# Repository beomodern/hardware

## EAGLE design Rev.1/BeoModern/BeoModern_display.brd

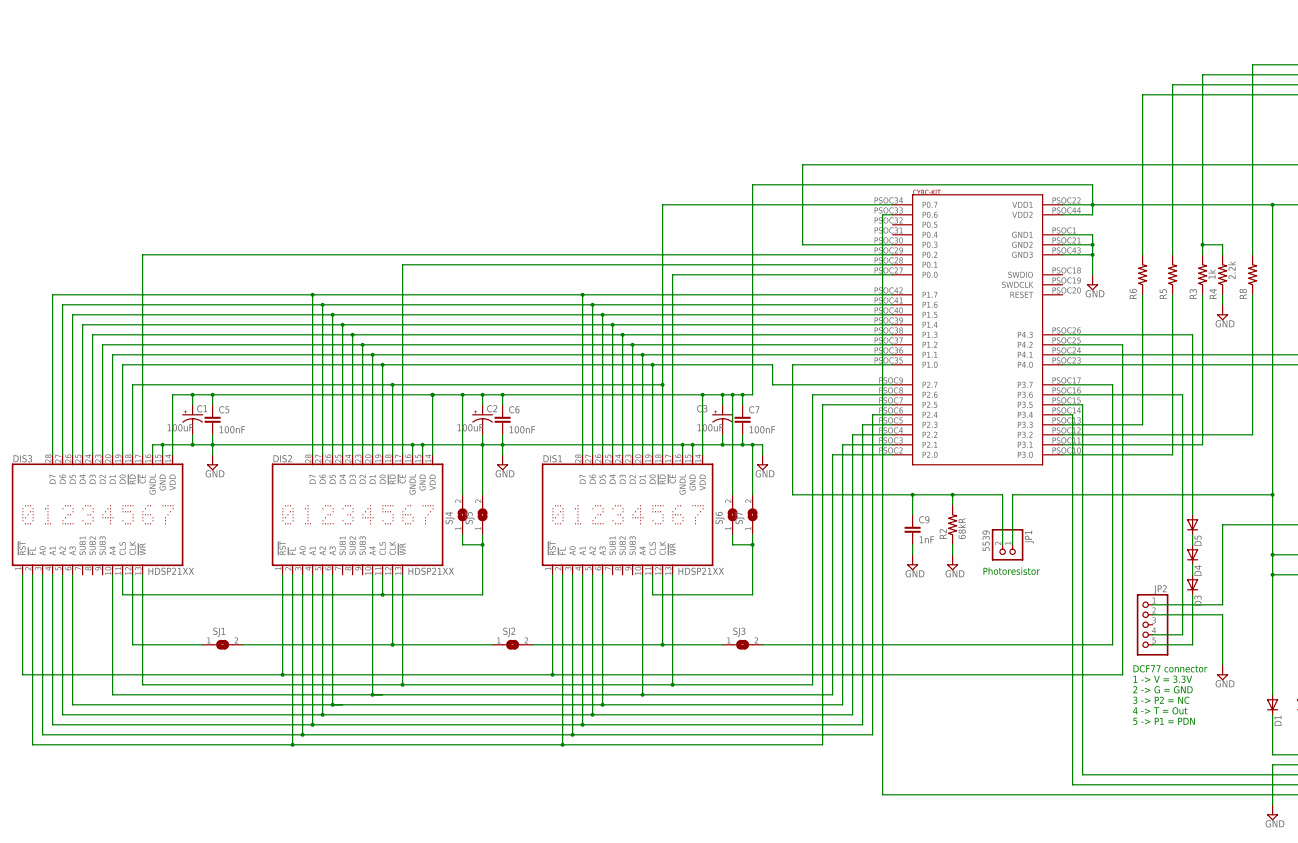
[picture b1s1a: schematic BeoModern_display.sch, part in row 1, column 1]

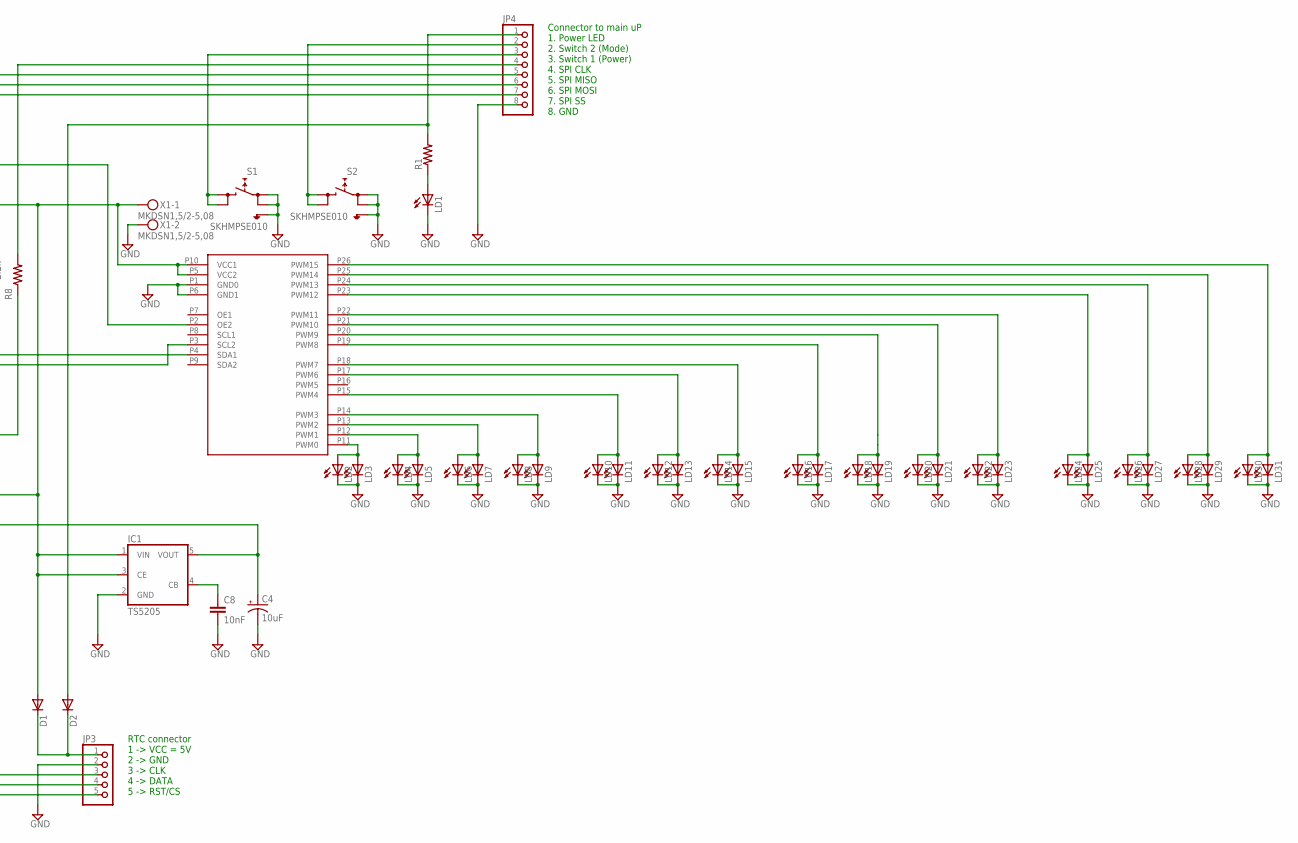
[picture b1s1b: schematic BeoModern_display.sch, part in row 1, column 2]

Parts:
C1, C2, C3: 100uF; E15-5
C4: 10uF; E2,5-5
C5, C6, C7: 100nF; C15B5
C8: 10nF; C2.5-2
C9: 1nF; C2.5-2
D1, D2, D3, D4, D5: DIODE-SOD80C; SOD80C
DIS1, DIS2, DIS3: HDSP21XX
IC1: TS5205; SOT25
JP1: 5539; 1X02
JP2, JP3: PINHD-1X5; 1X05
JP4: PINHD-1X8; 1X08
LD1, LD2, LD3, LD4, LD5, LD6, LD7, LD8, LD9, LD10, LD11, LD12, LD13, LD14, LD15, LD16, LD17, LD18, LD19, LD20, LD21, LD22, LD23, LD24, LD25, LD26, LD27, LD28, LD29, LD30, LD31: TLLR4400; LED3MM
R1, R5, R6, R8: R-US_0207/10; 0207/10
R2: 68kR; 0207/10
R3: 1k; 0207/10
R4: 2.2k; 0207/10
S1, S2: SKHMPSE010; SKHMPXE010
SJ1, SJ2, SJ3, SJ4, SJ5, SJ6, SJ7: SJ
U$9: CY8C-KIT; CY8C-KIT-FOOTPRINT
U$10: PCA9685; PCA9685_FOOTPRINT
X1: MKDSN1,5/2-5,08

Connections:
GND: C1.-, C2.-, C3.-, C4.-, C5.2, C6.2, C7.2, C8.2, C9.2, DIS1.15 (GND), DIS1.16 (GNDL), DIS2.15 (GND), DIS2.16 (GNDL), DIS3.15 (GND), DIS3.16 (GNDL), IC1.2 (GND), JP2.2, JP3.2, JP4.8, LD1.K (C), LD2.K (C), LD3.K (C), LD4.K (C), LD5.K (C), LD6.K (C), LD7.K (C), LD8.K (C), LD9.K (C), LD10.K (C), LD11.K (C), LD12.K (C), LD13.K (C), LD14.K (C), LD15.K (C), LD16.K (C), LD17.K (C), LD18.K (C), LD19.K (C), LD20.K (C), LD21.K (C), LD22.K (C), LD23.K (C), LD24.K (C), LD25.K (C), LD26.K (C), LD27.K (C), LD28.K (C), LD29.K (C), LD30.K (C), LD31.K (C), R2.1, R4.1, S1.1 (1.1), S1.2 (1.2), S1.5 (SH), S2.1 (1.1), S2.2 (1.2), S2.5 (SH), SJ5.2, SJ7.2, U$9.PSOC1 (GND1), U$9.PSOC21 (GND2), U$9.PSOC43 (GND3), U$10.P1 (GND0), U$10.P6 (GND1), X1.2
unnamed: LD14.A, LD15.A, U$10.P18 (PWM7)
unnamed: LD12.A, LD13.A, U$10.P17 (PWM6)
unnamed: U$9.PSOC24 (P4.1), U$10.P4 (SDA1)
unnamed: LD10.A, LD11.A, U$10.P15 (PWM4)
unnamed: LD1.A, R1.1
unnamed: JP2.4, U$9.PSOC16 (P3.6)
unnamed: U$9.PSOC23 (P4.0), U$10.P3 (SCL2)
unnamed: R5.1, U$9.PSOC10 (P3.0)
unnamed: LD30.A, LD31.A, U$10.P26 (PWM15)
unnamed: LD28.A, LD29.A, U$10.P25 (PWM14)
unnamed: LD26.A, LD27.A, U$10.P24 (PWM13)
unnamed: LD24.A, LD25.A, U$10.P23 (PWM12)
unnamed: R6.1, U$9.PSOC13 (P3.3)
unnamed: R8.1, U$9.PSOC12 (P3.2)
unnamed: JP4.6, R5.2
unnamed: JP4.4, R8.2
unnamed: JP4.7, R6.2
unnamed: DIS2.11 (CLS), DIS3.11 (CLS), SJ4.1, SJ5.1
unnamed: C8.1, IC1.4 (CB)
unnamed: JP4.2, S2.3 (2.1), S2.4 (2.2)
unnamed: D2.A, JP4.1, R1.2
unnamed: JP4.5, R3.2, R4.2
unnamed: DIS2.12 (CLK), SJ1.2, SJ2.1
unnamed: R3.1, U$9.PSOC11 (P3.1)
unnamed: SJ3.2, U$9.PSOC17 (P3.7)
unnamed: DIS1.12 (CLK), SJ2.2, SJ3.1
unnamed: DIS1.11 (CLS), SJ6.1, SJ7.1
unnamed: DIS3.12 (CLK), SJ1.1
unnamed: DIS1.19 (D0), DIS2.19 (D0), DIS3.19 (D0), U$9.PSOC9 (P2.7)
unnamed: DIS1.13 (!WR), DIS2.13 (!WR), DIS3.13 (!WR), U$9.PSOC8 (P2.6)
unnamed: DIS1.28 (D7), DIS2.28 (D7), DIS3.28 (D7), U$9.PSOC42 (P1.7)
unnamed: DIS1.27 (D6), DIS2.27 (D6), DIS3.27 (D6), U$9.PSOC41 (P1.6)
unnamed: DIS1.26 (D5), DIS2.26 (D5), DIS3.26 (D5), U$9.PSOC40 (P1.5)
unnamed: DIS1.25 (D4), DIS2.25 (D4), DIS3.25 (D4), U$9.PSOC39 (P1.4)
unnamed: DIS1.24 (D3), DIS2.24 (D3), DIS3.24 (D3), U$9.PSOC38 (P1.3)
unnamed: DIS1.23 (D2), DIS2.23 (D2), DIS3.23 (D2), U$9.PSOC37 (P1.2)
unnamed: DIS1.20 (D1), DIS2.20 (D1), DIS3.20 (D1), U$9.PSOC36 (P1.1)
unnamed: DIS1.18 (!RD), DIS2.18 (!RD), DIS3.18 (!RD), U$9.PSOC34 (P0.7)
unnamed: DIS3.17 (!CE), U$9.PSOC29 (P0.2)
unnamed: DIS2.17 (!CE), U$9.PSOC28 (P0.1)
unnamed: DIS1.17 (!CE), U$9.PSOC27 (P0.0)
unnamed: DIS1.10 (A4), DIS2.10 (A4), DIS3.10 (A4), U$9.PSOC2 (P2.0)
unnamed: DIS1.1 (!RST), DIS2.1 (!RST), DIS3.1 (!RST), U$9.PSOC25 (P4.2)
unnamed: DIS1.6 (A3), DIS2.6 (A3), DIS3.6 (A3), U$9.PSOC3 (P2.1)
unnamed: DIS1.5 (A2), DIS2.5 (A2), DIS3.5 (A2), U$9.PSOC4 (P2.2)
unnamed: DIS1.4 (A1), DIS2.4 (A1), DIS3.4 (A1), U$9.PSOC5 (P2.3)
unnamed: DIS1.3 (A0), DIS2.3 (A0), DIS3.3 (A0), U$9.PSOC6 (P2.4)
unnamed: DIS1.2 (!FL), DIS2.2 (!FL), DIS3.2 (!FL), U$9.PSOC7 (P2.5)
unnamed: U$9.PSOC30 (P0.3), U$10.P2 (OE2)
unnamed: D5.A, U$9.PSOC26 (P4.3)
unnamed: LD22.A, LD23.A, U$10.P22 (PWM11)
unnamed: LD20.A, LD21.A, U$10.P21 (PWM10)
unnamed: LD18.A, LD19.A, U$10.P20 (PWM9)
unnamed: LD16.A, LD17.A, U$10.P19 (PWM8)
unnamed: LD8.A, LD9.A, U$10.P14 (PWM3)
unnamed: LD6.A, LD7.A, U$10.P13 (PWM2)
unnamed: LD4.A, LD5.A, U$10.P12 (PWM1)
unnamed: LD2.A, LD3.A, U$10.P11 (PWM0)
unnamed: C4.+, IC1.5 (VOUT), JP2.1
unnamed: JP4.3, S1.3 (2.1), S1.4 (2.2)
unnamed: C9.1, JP1.2, R2.2, U$9.PSOC35 (P1.0)
unnamed: JP3.3, U$9.PSOC15 (P3.5)
unnamed: JP3.4, U$9.PSOC14 (P3.4)
unnamed: JP3.5, U$9.PSOC33 (P0.6)
unnamed: D3.C, JP2.5
unnamed: D4.A, D5.C
unnamed: D3.A, D4.C
unnamed: D1.C, D2.C, JP3.1
unnamed: C1.+, C2.+, C3.+, C5.1, C6.1, C7.1, D1.A, DIS1.14 (VDD), DIS2.14 (VDD), DIS3.14 (VDD), IC1.1 (VIN), IC1.3 (CE), JP1.1, SJ4.2, SJ6.2, U$9.PSOC22 (VDD1), U$9.PSOC44 (VDD2), U$10.P5 (VCC2), U$10.P10 (VCC1), X1.1

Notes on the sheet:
DCF77 connector 1 -> V = 3.3V 2 -> G = GND 3 -> P2 = NC 4 -> T = Out 5 -> P1 = PDN
RTC connector 1 -> VCC = 5V 2 -> GND 3 -> CLK 4 -> DATA 5 -> RST/CS
Photoresistor
Connector to main uP 1. Power LED 2. Switch 2 (Mode) 3. Switch 1 (Power) 4. SPI CLK 5. SPI MISO 6. SPI MOSI 7. SPI SS 8. GND

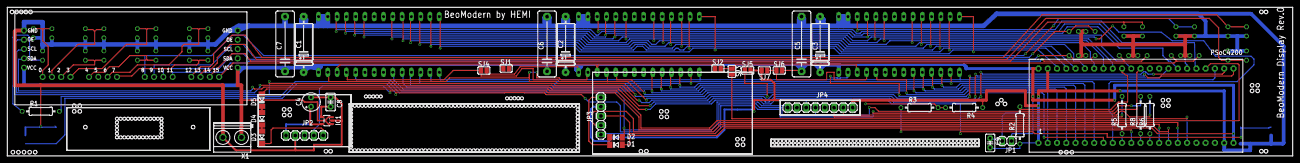
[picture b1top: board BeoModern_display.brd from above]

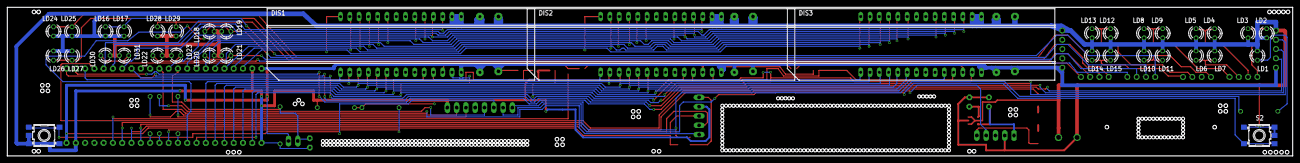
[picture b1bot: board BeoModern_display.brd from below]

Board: 2 copper layers, 351.5 x 40.6 mm, 72 parts (36 on the bottom side), 70 nets.
